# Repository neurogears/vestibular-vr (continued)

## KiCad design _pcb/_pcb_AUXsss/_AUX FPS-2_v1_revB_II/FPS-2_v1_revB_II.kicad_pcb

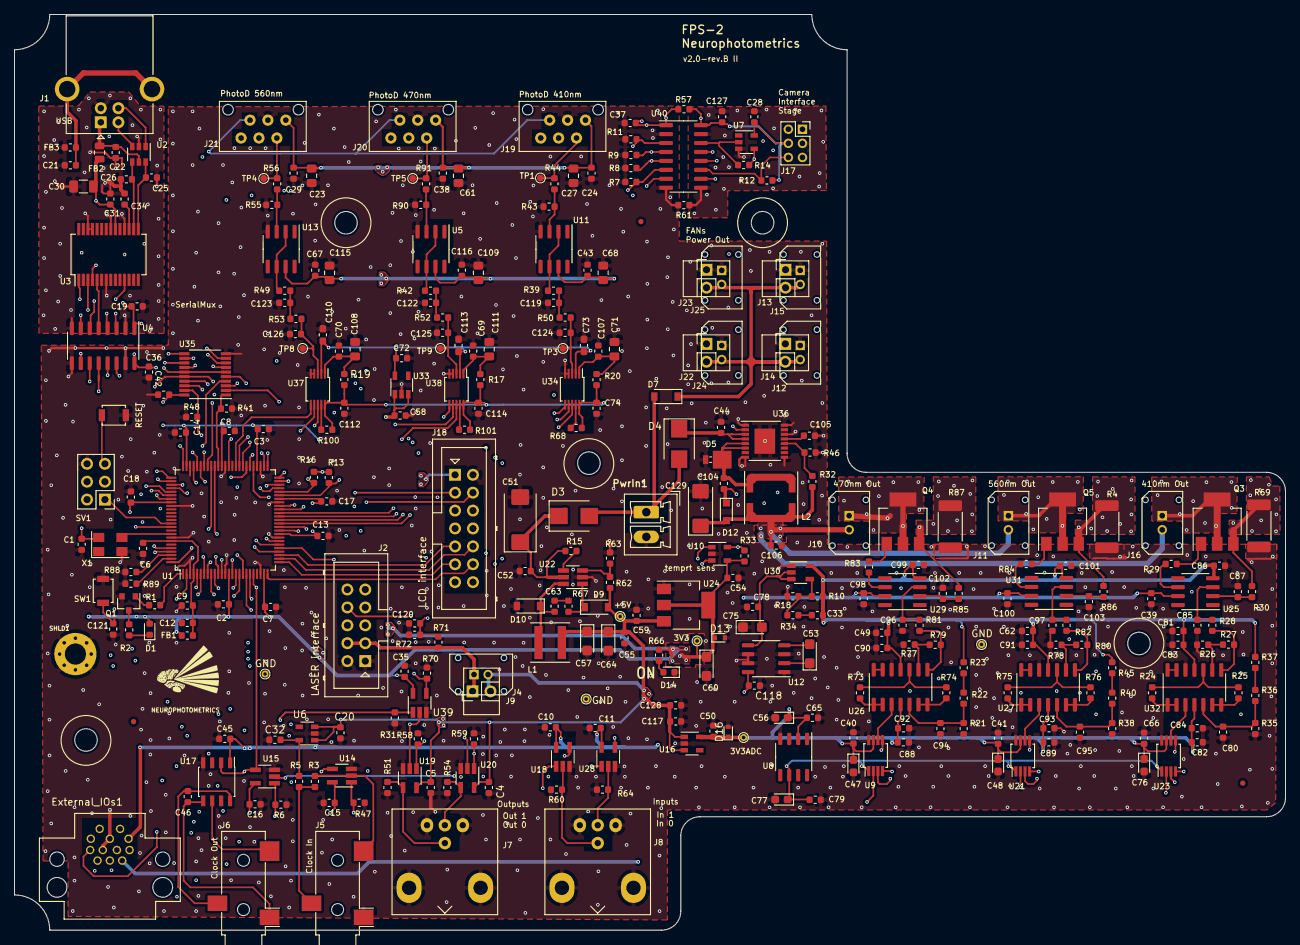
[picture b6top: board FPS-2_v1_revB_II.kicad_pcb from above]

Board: 4 copper layers, 180.4 x 130.0 mm, 335 parts (0 on the bottom side), 210 nets.

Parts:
Adafruit 2.8'' LCD: Adafruit_2.8''_LCD
C1, C2, C3, C4, C5, C6, C7, C8, C9, C10, C11, C13, C14, C15, C16, C17, C18, C19, C22, C24, C28, C29, C31, C34, C35, C36, C37, C38, C39, C40, C41, C42, C43, C45, C46, C52, C54, C55, C58, C63, C65, C66, C67, C69, C70, C72, C74, C79, C80, C83, C84, C86, C90, C91, C92, C93, C94, C95, C98, C99, C100, C101, C107, C112, C114, C116, C120, C121, C127, C128: 100n; C_0603_1608Metric
C12: 330n; C_0603_1608Metric
C20, C32, C49, C50, C62, C78, C81, C82, C88, C89, C106, C118: 4.7u 16V; C_0603_1608Metric
C21, C59: 4.7nF; C_0603_1608Metric
C23, C27, C61, C68, C71, C108, C109, C111, C115: 10u 16V; C_0805_2012Metric_Pad1.15x1.40mm_HandSolder
C25, C26: 47p; C_0603_1608Metric
C30: 4.7u 10V; C_1206_3216Metric
C33, C85, C87, C96, C97, C102, C103, C119, C122, C123, C124, C125, C126: DNI; C_0603_1608Metric
C44: 2.2u; C_0603_1608Metric
C47, C48, C56, C76, C77: 1u 25V; CP_EIA-2012-12_Kemet-R
C51: 10u 50V; CP_EIA-7343-20_Kemet-V_Pad2.25x2.55mm_HandSolder
C53, C57, C60, C64, C75: 10u 10V; CP_EIA-3216-18_Kemet-A
C73, C110, C113: 4.7u 16V; C_0603_1608Metric_Pad1.05x0.95mm_HandSolder
C104: 180nF; C_0603_1608Metric
C105: 2.2nF; C_0603_1608Metric
C117: 180pF; C_0603_1608Metric
C129: 100uF 25V; CP_EIA-6032-28_Kemet-C
D1, D14: GREEN LED; LED_0603_1608Metric
D3, D4: SSB43L-E3; D_SMB
D5: MBRM120; D_Powermite_AK
D7: SS14FL; D_SOD-123
D9: 1N4148W; D_SOD-123
D10: BAT42W-V; D_SOD-123
D12: CMDSH-3; D_SOD-323_HandSoldering
D13, D16: ESD9X3.3ST5G; D_SOD-523
External_IOs1: Conn_01x012; Phoenix_1424194_12pin
FB1: 330 R; R_0603_1608Metric
FB2: 40R@100MHz; R_0805_2012Metric
FB3: 600R/100MHz; R_0603_1608Metric
FID1, FID2, FID3: Fiducial; Fiducial_0.75mm_Mask1.5mm
G1: Neurophotometrics_Logo
J1: my_USB_B; my_USB_B_OST_USB-B1HSxx_Horizontal
J2: Conn_02x05_Odd_Even; Multicomp_MC9A12-1034_2x05_P2.54mm_Vertical
J4, J10, J11, J16: M80_1x2_2mmP; my_PinHeader_M80_1x2_2mmP
J5, J6: AudioJack2_Reference; my_Jack_3.5mm_CUI_SJ-3523-SMT_Horizontal
J7, J8: my_Conn_Coaxial_x2; my_2_BNC
J9, J13, J14, J22, J23: DNI; my_PinHeader_1x02_P2.54mm_Vertical
J12, J15, J24, J25: B2B plug; my_PinHeader_M80_1x2_2mmP
J17: Conn_02x03_Odd_Even; PinSocket_2x03_P2.00mm_Vertical
J18: Conn_02x07_Odd_Even; Multicomp_MC9A12-1434_2x07_P2.54mm_Vertical
J19, J20, J21: Molex_90325-3006
L1: 22uL; L_Coilcraft_XAL5030
L2: 2.6uL 1A; L_Coilcraft_XAL5030
Mech1, Mech2, Mech3, Mech4, Mech5: MountingHole_3.2mm_M3
PwrIn1: PowerIn; PhoenixContact_MCV_1,5_2-G-3.5_1x02_P3.50mm_Vertical
Q1: BC850; SOT-23
Q3, Q4, Q5: BCP56T1G; SOT-223-3_TabPin2
R1, R23, R37, R45: 1k; R_0603_1608Metric
R2, R66: 330R; R_0603_1608Metric
R3, R6, R7, R8, R9, R11, R31, R41, R47, R48, R51, R54, R58, R59, R60, R64, R70, R88, R89: 100k; R_0603_1608Metric
R4, R69, R87: 1R; R_2512_6332Metric_Pad1.52x3.35mm_HandSolder
R5, R17, R19, R20, R39, R42, R44, R49, R56, R91: 10R; R_0603_1608Metric
R10, R21, R35, R38: 5.76k; R_0603_1608Metric
R12, R33, R46, R63, R71: 10k; R_0603_1608Metric
R13: 2k8; R_0603_1608Metric
R14, R28, R29, R30, R50, R52, R53, R68, R81, R82, R83, R84, R85, R86, R100, R101: 0R; R_0603_1608Metric
R15: 1M; R_0603_1608Metric
R16, R34, R43, R55, R57, R61, R90: DNI; R_0603_1608Metric
R18: 86.6k; R_0603_1608Metric
R22, R36, R40, R72: 18k; R_0603_1608Metric
R24, R25, R26, R27, R73, R74, R75, R76, R77, R78, R79, R80: 4k7; R_0603_1608Metric
R32: 36k; R_0603_1608Metric
R62: 52.3k; R_0603_1608Metric
R67: 100R; R_0603_1608Metric
SHLD1: TestPoint_Probe; MountingHole_3mm_Pad_Via
SV1: MA03-2; PinHeader_2x03_P2.54mm_Vertical
SW1, SW2: SW_DIP_x01; SW_SPST_B3U-1000P
TP1, TP3, TP4, TP5, TP8, TP9: TestPoint; TestPoint_Pad_D1.0mm
TP10, TP20, TP21, TP22, TP23, TP24: TestPoint_Probe; TestPoint_THTPad_D1.0mm_Drill0.5mm
U1: ATxmega128A1U; TQFP-100_14x14mm_P0.5mm
U2: USBLC6-2; SOT-23-6
U3: FT232RL; SSOP-28_5.3x10.2mm_P0.65mm
U4: SI8642BC-B-IS1; SOIC-16_3.9x9.9mm_P1.27mm
U5, U11, U13: AD8655; SOIC-8_3.9x4.9mm_P1.27mm
U6: TLV70033_SOT23-5; SOT-23-5
U7: DNI; SOT-23-5
U8: MAX6162; SO-8_3.9x4.9mm_P1.27mm
U9, U21, U23: MAX5443; MSOP-8_3x3mm_P0.65mm
U10: Si7060; SOT-23-5
U12: MAX1680ESA+; SO-8_3.9x4.9mm_P1.27mm
U14, U15, U19, U20, U39: MC74VHC1GT126; SOT-23-5_HandSoldering
U16: TLV7433; SOT-23-5
U17: Si8610BC; SOIC-8_3.9x4.9mm_P1.27mm
U18, U28: SN74LVC1g125; SOT-23-5_HandSoldering
U22: MCP16301; SOT-23-6_Handsoldering
U24: LD1117S33TR; SOT-223-3_TabPin2
U25, U29, U31: AD8651; SOIC-8_3.9x4.9mm_P1.27mm
U26, U27, U32: OPA4170AIDR; SOIC-14_3.9x8.7mm_P1.27mm
U30: ADP7182AUJZ; TSOT-23-5
U33: TCR2LF; TSOT-23-5
U34, U37, U38: MCP33151D; MSOP-10_3x3mm_P0.5mm
U35: SN74ACT241; TSSOP-20_4.4x6.5mm_P0.65mm
U36: LT1765; TSSOP-16-1EP_4.4x5mm_P0.65mm
U40: SI8641; SOIC-16_3.9x9.9mm_P1.27mm
Wall: Stub_Wall
X1: DSC1001CI5-032; Crystal_SMD_5032-4Pin_5.0x3.2mm

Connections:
5V5_LEDS_POWER: C106.1, C129.1, D12.2, J10.2, J11.2, J16.2, L2.2, R32.1
+1V8: C72.1, C73.1, C110.1, C113.1, U33.5, U34.2, U37.2, U38.2
+3.3VDAC: C39.2, C40.2, C41.2, C47.1, C48.1, C50.2, C56.1, C65.2, C66.2, C76.1, C82.2, C84.2, C88.2, C89.2, C92.2, C93.2, C98.2, C100.2, C118.2, D16.1, TP10.1, U8.2, U9.7, U12.8, U16.5, U21.7, U23.7, U25.7, U26.4, U27.4, U29.7, U31.7, U32.4
+3.3VP: J5.R, R3.1, R5.1
+3V3: C1.2, C2.2, C3.2, C7.2, C8.2, C10.2, C11.2, C13.2, C14.2, C15.2, C16.2, C17.2, C18.2, C23.1, C24.1, C27.1, C29.1, C35.2, C36.2, C37.2, C38.1, C42.2, C43.1, C45.2, C54.2, C58.1, C60.1, C61.1, C67.1, C68.1, C74.1, C109.1, C112.1, C114.1, C115.1, C116.1, D1.2, D13.1, External_IOs1.9, FB1.2, J19.1, J20.1, J21.1, R13.2, R16.2, R17.1, R19.1, R20.1, R33.1, R57.2, R66.1, R68.1, R100.1, R101.1, SV1.2, TP24.1, U1.14, U1.24, U1.34, U1.44, U1.54, U1.64, U1.74, U1.83, U4.10, U4.16, U5.7, U10.4, U11.7, U13.7, U14.5, U15.5, U17.1, U18.5, U24.2, U28.5, U33.1, U33.3, U34.10, U35.20, U37.10, U38.10, U39.5, U40.1, U40.7, X1.4
+5V: C4.2, C5.2, C20.2, C55.1, C57.1, C59.1, C64.1, C117.2, C128.2, D9.2, J4.2, J9.2, J18.1, L1.2, R62.1, TP21.1, U6.1, U6.3, U16.1, U16.3, U19.5, U20.5, U24.3
-VDC: C33.2, C49.2, C62.2, C81.2, C83.2, C86.2, C90.2, C91.2, C99.2, C101.2, R10.1, R23.2, R37.2, R45.2, U25.4, U26.11, U27.11, U29.4, U30.5, U31.4, U32.11
/CLOCK_MASTER: J18.14, U1.21, U14.4, U15.4, U17.2
/COM_FROM_USB: J18.8, U1.66
/HOLD_COM: J18.7, U1.67
/I2C_SCL_port_Y: R16.1, U1.46, U10.3
/I2C_SDA_port_Y: R13.1, U1.45, U10.1
/IO_Interfaces/CAM_GND: C28.1, C127.1, J17.3, R61.1, U7.3, U40.9, U40.15
/IO_Interfaces/CAM_OUT_1: J17.1, U40.13
/IO_Interfaces/CAM_OUT_2: J17.2, U40.12
/IO_Interfaces/CAM_POWER: C28.2, C127.2, J17.4, R12.1, R57.1, U7.5, U40.10, U40.16
/IO_Interfaces/CAM_STROB_IN: J17.6, R12.2, U40.11
/IO_Interfaces/CAM_TRIG_OUT: R14.2, U7.2, U40.14
/IO_Interfaces/CAM_TRIG_OUT_BUFF: J17.5, R14.1, U7.4
/IO_Interfaces/CLOCK_IN: J5.T, R3.2, U14.2
/IO_Interfaces/CLOCK_OUT: J6.T, U17.6
/IO_Interfaces/CLOCK_OUT_GND: C46.1, J6.S, U17.5
/IO_Interfaces/CLOCK_OUT_Vcc: C46.2, J6.R, U17.8
/IO_Interfaces/FT_CTS: U3.11, U4.6
/IO_Interfaces/FT_RTS: U3.3, U4.4
/IO_Interfaces/FT_RXD: U3.5, U4.5
/IO_Interfaces/FT_TXD: U3.1, U4.3
/IO_Interfaces/LASER_Power: J2.3, J2.4, J4.1, J9.1, R71.1
/IO_Interfaces/LASER_TTL: J2.8, R70.2, U39.4
/IO_Interfaces/USB5V: C19.2, C30.1, C31.2, FB2.1, U3.4, U3.20, U4.1, U4.7
/IO_Interfaces/USBDM: C26.2, U2.4, U3.16
/IO_Interfaces/USBDP: C25.2, U2.6, U3.15
/LCD_CLCK_OUT: J18.13, U15.2
/LCD_Clock_Out_ENBL: R6.1, U1.6, U15.1
/LEDs_output_Interface/-3V3: C75.2, C78.2, U12.5, U30.2, U30.3
/LEDs_output_Interface/CURR_410nm: U23.6, U32.3
/LEDs_output_Interface/CURR_470nm: U9.6, U26.3
/LEDs_output_Interface/CURR_560nm: U21.6, U27.3
/LEDs_output_Interface/LED_CTRL_410nm: R27.2, R28.1, U32.8
/LEDs_output_Interface/LED_CTRL_470nm: R79.2, R81.1, U26.8
/LEDs_output_Interface/LED_CTRL_560nm: R80.2, R82.1, U27.8
/LEDs_output_Interface/Vref_2.048V: C77.1, C79.2, U8.6, U9.1, U21.1, U23.1
/MASTER_CTS: J18.12, U1.25
/MASTER_RTS: J18.11, U1.26
/MASTER_RXD: J18.10, U1.27
/MASTER_TXD: J18.9, U1.28
/PDI_CLK: SV1.5, SW2.2, U1.90
/PDI_DATA: SV1.1, U1.89
/PSU_Stage/FAN_POWER: D7.1, J12.2, J13.2, J14.2, J15.2, J22.2, J23.2, J24.2, J25.2
/PhotoD_410nm_SPI_MISO: U1.38, U34.7
/PhotoD_410nm_SPI_SCLK: U1.37, U34.8
/PhotoD_470nm_SPI_MISO: U1.40, U38.7
/PhotoD_470nm_SPI_SCLK: U1.39, U38.8
/PhotoD_560nm_SPI_MISO: U1.42, U37.7
/PhotoD_560nm_SPI_SCLK: U1.41, U37.8
/PhotoDiodes input Interface/PhotodiodeLP_410nm: C124.1, R50.2, TP3.1, U34.3
/PhotoDiodes input Interface/PhotodiodeLP_470nm: C125.1, R52.2, TP9.1, U38.3
/PhotoDiodes input Interface/PhotodiodeLP_560nm: C126.1, R53.2, TP8.1, U37.3
/PhotoDiodes input Interface/PhotodiodeOutput_410nm: J19.2, R44.2, TP1.1
/PhotoDiodes input Interface/PhotodiodeOutput_470nm: J20.2, R91.1, TP5.1
/PhotoDiodes input Interface/PhotodiodeOutput_560nm: J21.2, R56.2, TP4.1
/aux_IO1: R88.2, U1.98
/aux_IO2: R89.2, U1.99
/mux_CTS: U4.13, U35.8, U35.17
/mux_RTS: U4.11, U35.7, U35.16
/mux_RXD: U4.14, U35.6, U35.15
/mux_TXD: U4.12, U35.9, U35.18
/tempert_ALARM1: R33.2, U1.69, U10.5
/u_CAM_OUT_1: R9.2, U1.50, U40.4
/u_CAM_OUT_2: R8.2, U1.49, U40.5
/u_CAM_STROB_IN: R7.2, U1.57, U40.6
/u_CAM_TRIG_OUT: R11.2, U1.15, U40.3
/u_CTS_0: U1.71, U35.12
/u_CTS_1: J18.5, U35.3
/u_Clck_In_Enable: R47.1, U1.5, U14.1
/u_DigPot_410_~CS: J19.4, U1.68
/u_DigPot_470_~CS: J20.4, U1.70
/u_DigPot_560_~CS: J21.4, U1.72
/u_DigPot_SPI_CLCK: J19.6, J20.6, J21.6, U1.76
/u_DigPot_SPI_SDO: J19.5, J20.5, J21.5, U1.77
/u_External_IO_1: External_IOs1.1, U1.29
/u_External_IO_2: External_IOs1.3, U1.31
/u_External_IO_3: External_IOs1.5, U1.51
/u_External_IO_4: External_IOs1.12, U1.52
/u_External_IO_5: External_IOs1.2, U1.96
/u_External_IO_6: External_IOs1.4, U1.97
/u_External_UART_Rx: External_IOs1.6, U1.17
/u_External_UART_Tx: External_IOs1.8, U1.18
/u_In6: U1.56, U18.4
/u_In6_Enbl: U1.80, U18.1
/u_In7: U1.81, U28.4
/u_In7_Enbl: U1.82, U28.1
/u_LASER_state_ON_OFF: C120.2, R71.2, R72.1, U1.100
/u_LEDs_DAC_SPI_CLK_out: U1.32, U9.3, U21.3, U23.3
/u_LEDs_DAC_SPI_MOSI: U1.30, U9.4, U21.4, U23.4
/u_Out4: U1.35, U19.2, U39.2
/u_Out4_Enbl: R58.2, U1.78, U19.1
/u_Out5: U1.36, U20.2
/u_Out5_Enbl: R59.2, U1.79, U20.1
/u_Out6_LASER_ENBL: R31.2, U1.55, U39.1
/u_PhotoD_ADC_ConverStart_410nm: U1.58, U34.6
/u_PhotoD_ADC_ConverStart_470nm: U1.59, U38.6
/u_PhotoD_ADC_ConverStart_560nm: U1.60, U37.6
/u_RTS_0: U1.75, U35.4
/u_RTS_1: J18.6, U35.13
/u_RXD_0: U1.47, U35.14
/u_RXD_1: J18.3, U35.5
/u_STATE_LED: R1.1, U1.1
/u_TXD_0: U1.48, U35.2
/u_TXD_1: J18.4, U35.11
/u_interface_select_1: R41.2, U1.65, U35.1
/u_interface_select_2: R48.2, U1.62, U35.19
/u_test_switch_1: C121.2, SW1.1, U1.2
/~u_DAC_CLR_410nm: U1.8, U23.5
/~u_DAC_CLR_470nm: U1.12, U9.5
/~u_DAC_CLR_560nm: U1.10, U21.5
/~u_DAC_CS_410nm: U1.7, U23.2
/~u_DAC_CS_470nm: U1.11, U9.2
/~u_DAC_CS_560nm: U1.9, U21.2
/~u_LASER_CS: J2.5, U1.16
/~u_LASER_SPI_CLCK: J2.6, U1.19
/~u_LASER_SPI_DATA: J2.7, U1.20
GNDD: C1.1, C2.1, C3.1, C4.1, C5.1, C6.1, C7.1, C8.1, C9.1, C10.1, C11.1, C12.1, C13.1, C14.1, C15.1, C16.1, C17.1, C18.1, C20.1, C23.2, C24.2, C27.2, C29.2, C32.1, C35.1, C36.1, C37.1, C38.2, C39.1, C40.1, C41.1, C42.1, C43.2, C44.2, C45.1, C47.2, C48.2, C49.1, C50.1, C51.2, C52.2, C54.1, C55.2, C56.2, C57.2, C58.2, C59.2, C60.2, C61.2, C62.1, C64.2, C65.1, C66.1, C67.2, C68.2, C69.2, C70.2, C71.2, C72.2, C73.2, C74.2, C75.1, C76.2, C77.2, C78.1, C79.1, C80.1, C81.1, C82.1, C83.1, C84.1, C85.1, C86.1, C87.1, C88.1, C89.1, C90.1, C91.1, C92.1, C93.1, C94.1, C95.1, C96.1, C97.1, C98.1, C99.1, C100.1, C101.1, C102.1, C103.1, C105.2, C106.2, C107.2, C108.2, C109.2, C110.2, C111.2, C112.2, C113.2, C114.2, C115.2, C116.2, C117.1, C118.1, C119.2, C120.1, C121.1, C122.2, C123.2, C124.2, C125.2, C126.2, C128.1, C129.2, D5.2, D10.2, D13.2, D14.1, D16.2, External_IOs1.10, External_IOs1.11, J2.1, J2.2, J5.S, J7.3, J8.3, J12.1, J13.1, J14.1, J15.1, J18.2, J19.3, J20.3, J21.3, J22.1, J23.1, J24.1, J25.1, PwrIn1.2, Q1.2, R4.2, R6.2, R7.1, R8.1, R9.1, R11.1, R18.1, R21.1, R26.1, R31.1, R35.1, R38.1, R41.1, R43.1, R46.2, R47.2, R48.1, R51.1, R54.1, R55.1, R58.1, R59.1, R60.2, R61.2, R63.2, R64.2, R69.2, R70.1, R72.2, R77.1, R78.1, R87.2, R88.1, R89.1, R90.1, SHLD1.1, SV1.6, SW1.2, SW2.1, TP20.1, TP22.1, TP23.1, U1.3, U1.13, U1.23, U1.33, U1.43, U1.53, U1.63, U1.73, U1.84, U1.93, U4.9, U4.15, U5.4, U6.2, U8.4, U9.8, U10.2, U11.4, U12.1, U12.3, U12.6, U12.7, U13.4, U14.3, U15.3, U16.2, U17.4, U18.3, U19.3, U20.3, U21.8, U22.2, U23.8, U24.1, U26.12, U27.12, U28.3, U30.1, U32.12, U33.2, U34.4, U34.5, U35.10, U36.1, U36.8, U36.9, U36.14, U36.16, U36.17, U37.4, U37.5, U38.4, U38.5, U39.3, U40.2, U40.8, X1.2
GNDREF: C19.1, C21.1, C22.1, C25.1, C26.1, C30.2, C31.1, C34.1, FB3.1, J1.4, U2.2, U3.7, U3.18, U3.21, U3.25, U3.26, U4.2, U4.8
unnamed: C6.2, C9.2, C12.2, FB1.1, U1.4, U1.94
unnamed: C21.2, FB3.2, J1.5
unnamed: C22.2, FB2.2, J1.1, U2.5
unnamed: C32.2, R5.2, U6.5
unnamed: C33.1, R34.1
unnamed: C34.2, U3.17
unnamed: C44.1, D4.1, U36.3, U36.4
unnamed: C51.1, C52.1, D3.1, R15.1, U22.5
unnamed: C53.1, U12.2
unnamed: C53.2, U12.4
unnamed: C63.1, D10.1, L1.1, U22.6
unnamed: C63.2, R67.2
unnamed: C80.2, R35.2, R36.1, U32.5
unnamed: C85.2, R28.2, U25.3
unnamed: C87.2, R30.1, U25.2
unnamed: C94.2, R21.2, R22.1, U26.5
unnamed: C95.2, R38.2, R40.1, U27.5
unnamed: C96.2, R81.2, U29.3
unnamed: C97.2, R82.2, U31.3
unnamed: C102.2, R85.1, U29.2
unnamed: C103.2, R86.1, U31.2
unnamed: C104.1, D12.1, U36.2
unnamed: C104.2, D5.1, L2.1, U36.5, U36.6
unnamed: C105.1, U36.13
unnamed: C71.1, C107.1, R20.2, U34.1
unnamed: C70.1, C108.1, R19.2, U37.1
unnamed: C69.1, C111.1, R17.2, U38.1
unnamed: C119.1, R39.2, R50.1
unnamed: C122.1, R42.2, R52.1
unnamed: C123.1, R49.2, R53.1
unnamed: D1.1, R2.1
unnamed: D9.1, R67.1, U22.1
unnamed: D14.2, R66.2
unnamed: J1.2, U2.3
unnamed: J1.3, U2.1
unnamed: J7.1, R51.2, U19.4
unnamed: J7.2, R54.2, U20.4
unnamed: J8.1, R60.1, U18.2
unnamed: J8.2, R64.1, U28.2
unnamed: J10.1, Q4.2
unnamed: J11.1, Q5.2
unnamed: J16.1, Q3.2
unnamed: Q1.1, R1.2
unnamed: Q1.3, R2.2
unnamed: Q3.1, R29.2
unnamed: Q3.3, R30.2, R69.1
unnamed: Q4.1, R83.2
unnamed: Q4.3, R85.2, R87.1
unnamed: Q5.1, R84.2
unnamed: Q5.3, R4.1, R86.2
unnamed: R10.2, R18.2, R34.2, U30.4
unnamed: R15.2, U22.4
unnamed: R22.2, R23.1
unnamed: R24.1, U32.1, U32.2
unnamed: R24.2, R25.2, U32.10
unnamed: R25.1, U32.6, U32.7
unnamed: R26.2, R27.1, U32.9
unnamed: R29.1, U25.6
unnamed: R32.2, R46.1, U36.12
unnamed: R36.2, R37.1
unnamed: R39.1, U11.2, U11.6
unnamed: R40.2, R45.1
unnamed: R42.1, U5.2, U5.6
unnamed: R43.2, R44.1, U11.3
unnamed: R49.1, U13.2, U13.6
unnamed: R55.2, R56.1, U13.3
unnamed: R62.2, R63.1, U22.3
unnamed: R68.2, U34.9
unnamed: R73.1, U26.1, U26.2
unnamed: R73.2, R74.2, U26.10
unnamed: R74.1, U26.6, U26.7
unnamed: R75.1, U27.1, U27.2
unnamed: R75.2, R76.2, U27.10
unnamed: R76.1, U27.6, U27.7
unnamed: R77.2, R79.1, U26.9
unnamed: R78.2, R80.1, U27.9
unnamed: R83.1, U29.6
unnamed: R84.1, U31.6
unnamed: R90.2, R91.2, U5.3
unnamed: R100.2, U37.9
unnamed: R101.2, U38.9
unnamed: U1.92, X1.3
unnamed: U26.13, U26.14
unnamed: U27.13, U27.14
unnamed: U32.13, U32.14
POWER_IN: D3.2, D4.2, D7.2, External_IOs1.7, PwrIn1.1

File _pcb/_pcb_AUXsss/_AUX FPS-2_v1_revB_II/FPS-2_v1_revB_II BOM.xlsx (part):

Source: | Z:\My Drive\projects\fiber photometry system v2 (FPS-2)\pcb\FPS-2_v1_revB_I\FPS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
Date: | 43894.601006944446
Tool: | Eeschema (5.1.4)-1
Generator: | C:\Program Files\KiCad\bin\scripting\plugins/_my_bom_csv_grouped_Value_FootPrin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
Component Count: | 325
Ref | Qnty | Value | Footprint | Comment | Comment2 | Mnfct | MnfctCode | Provider | ProviderCode
C1, C6, C18, C14, C17, C8, C3, C13, C7, C2, C9, C42, C121, C52, C63, C55, C36, 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 | 70 | 100n | Capacitor_SMD:C_0603_1608Metric | 100n 50V | - | Yageo | CC603KRX7R9BB104 | Mouser | 603-CC603KRX7R9BB104
C12, | 1 | 330n | Capacitor_SMD:C_0603_1608Metric | 330n 50V | - | TDK | CGA3E3X5R1H334K080AB | Mouser | 810-CGA3E3X5R1H334KB
C26, C25, | 2 | 47p | Capacitor_SMD:C_0603_1608Metric | 47pF 50V C0G 5% | - | AVX | 06035A470JAT2A | Mouser | 581-06035A470J
C30, | 1 | 4.7u 10V | Capacitor_SMD:C_1206_3216Metric | CAP TANT 4.7uF 10V 10% | - | AVX | TAJA475K010 | Mouser | 581-TAJA475K010
C44, | 1 | 2.2u | Capacitor_SMD:C_0603_1608Metric | 2.2uF | - | Yageo | GRM188R61E225MA12D | Mouser | 81-GRM188R61E225MA2D
C51, | 1 | 10u 50V | Capacitor_Tantalum_SMD:CP_EIA-7343-20_Kemet-V_Pad2.25x2.55mm_HandSolder | 10u 50V 20% | - | AVX | T521D106M050ATE090 | Mouser | 80-T521D106M50ATE90
C56, C77, C76, C48, C47, | 5 | 1u 25V | Capacitor_Tantalum_SMD:CP_EIA-2012-12_Kemet-R | - | - | AVX | TPSR105K025R2500 | Mouser | 581-TPSR105K025R2500
C59, C21, | 2 | 4.7nF | Capacitor_SMD:C_0603_1608Metric | 4.7nF 50V X7R 10% | - | AVX | 06035C472KAT2A | Mouser | 581-06035C472K
C60, C57, C64, C53, C75, | 5 | 10u 10V | Capacitor_Tantalum_SMD:CP_EIA-3216-18_Kemet-A | Tantalum Capacitors - 10uF 10volts 20% A Case | - | Vishay | T55A106M010C0300 | Mouser | 74-T55A106M010C0300
C68, C115, C23, C108, C27, C111, C61, C71, C109, | 9 | 10u 16V | Capacitor_SMD:C_0805_2012Metric_Pad1.15x1.40mm_HandSolder | - | - | Taiyo Yuden | EMK212ABJ106MG-T | Mouser | 963-EMK212ABJ106MG-T
C73, C113, C110, | 3 | 4.7u 16V | Capacitor_SMD:C_0603_1608Metric_Pad1.05x0.95mm_HandSolder | Multilayer Ceramic SMD 0603 16V 4.7uF X6S | - | TDK | C1608X6S1C475K080AC | Mouser | 810-C1608X6S1C475K
C97, C103, C96, C102, C87, C85, C33, C123, C126, C122, C125, C119, C124, | 13 | DNI | Capacitor_SMD:C_0603_1608Metric | - | - | - | - | - | -
C104, | 1 | 180nF | Capacitor_SMD:C_0603_1608Metric | - | - | Murata Electronics | GRM188R71E184KA88D | Mouser | 81-GRM188R71E184KA8D
C105, | 1 | 2.2nF | Capacitor_SMD:C_0603_1608Metric | 2.2n | - | KEMET | C0603C222K3RACTU | Mouser | 80-C0603C222K3R
C106, C20, C32, C78, C89, C62, C88, C49, C81, C82, C50, C118, | 12 | 4.7u 16V | Capacitor_SMD:C_0603_1608Metric | Multilayer Ceramic SMD 0603 16V 4.7uF X6S | - | TDK | C1608X6S1C475K080AC | Mouser | 810-C1608X6S1C475K
C117, | 1 | 180pF | Capacitor_SMD:C_0603_1608Metric | 180pF 50V 5% | - | Yageo | C0603C181J5GACTU | Mouser | 80-C0603C181J5G
D1, D14, | 2 | GREEN LED | LED_SMD:LED_0603_1608Metric | Power On LED | - | Vishay | TLMP1100-GS08 | Mouser | 78-TLMP1100-GS08
D3, D4, | 2 | SSB43L-E3 | Diode_SMD:D_SMB | - | - | Vishay | SSB43L-E3/52T | Mouser | 625-SSB43L-E3
D5, | 1 | MBRM120 | Diode_SMD:D_Powermite_AK | ESD Protection Diode; | ref value UPS20 old; update to MBRM120LT3G | On Semiconductor | MBRM120LT3G | Mouser | 863-MBRM120LT3G
D7, | 1 | SS14FL | Diode_SMD:D_SOD-123 | - | - | ON Semiconductor | SS14FL | Mouser | 512-SS14FL
D9, | 1 | 1N4148W | Diode_SMD:D_SOD-123 | Diodes - General Purpose, Power, Switching 100 Volt 500mA 4ns | - | Vishay | 1N4148W-E3-18 | Mouser | 78-1N4148W-E3-18
D10, | 1 | BAT42W-V | Diode_SMD:D_SOD-123 | ESD Protection Diode | - | Vishay | BAT42W-G3-08 | Mouser | 78-BAT42W-G3-08
D12, | 1 | CMDSH-3 | Diode_SMD:D_SOD-323_HandSoldering | CMDSH-3 | - | Central Semiconductor | CMDSH-3 TR | Mouser | 610-CMDSH-3
D13, D16, | 2 | ESD9X3.3ST5G | Diode_SMD:D_SOD-523 | Low Voltage Transil =3V3 | - | ON Semiconductor | ESD9X3.3ST5G | Mouser | 863-ESD9X3.3ST5G
External_IOs1, | 1 | Conn_01x012 | FPS_pads_lib:Phoenix_1424194_12pin | TO BE SURE ABOUT THIS PLUG - MECHANICALLY & ELECTRICALLY | - | Phoenix Contact | 1424194 | Mouser | 651-1424194
F1, | 1 | 600R/100MHz | Resistor_SMD:R_0603_1608Metric | - | - | Yageo | BLM18KG601SN1D | Mouser | 81-BLM18KG601SN1D
FB1, | 1 | 330 R | Resistor_SMD:R_0603_1608Metric | Ferrite Beads 330ohms Power Supply | - | Murata Electronics | BLM18SG331TN1D | Mouser | 81-BLM18SG331TN1D
FB2, | 1 | 40R@100MHz | Resistor_SMD:R_0805_2012Metric | USB ferrite bead | - | Laird Performance Materials | MI0805K400R-10 | Mouser | 875-MI0805K400R-10
FID1, FID2, FID3, | 3 | Fiducial | Fiducial:Fiducial_0.75mm_Mask1.5mm | - | - | n.a. | n.a. | n.a. | n.a.
J1, | 1 | my_USB_B | FPS_pads_lib:my_USB_B_OST_USB-B1HSxx_Horizontal | USB B | - | Amphenol FCI | 61729-1011BLF | Mouser | 649-61729-1011BLF
J2, | 1 | Conn_02x05_Odd_Even | Connector_Multicomp:Multicomp_MC9A12-1034_2x05_P2.54mm_Vertical | LASER Header Interface 10P 4WALL GLDFL | - | 3M Electronic Solutions Division | 30310-6002HB | Mouser | 517-30310-6002
J4, J16, J11, J10, | 4 | M80_1x2_2mmP | FPS_pads_lib:my_PinHeader_M80_1x2_2mmP | 560nm output | - | Phoenix Contact | M80-8820242 | Mouser | 855-M80-8820242
J5, J6, | 2 | AudioJack2_Reference | FPS_pads_lib:my_Jack_3.5mm_CUI_SJ-3523-SMT_Horizontal | Clock_Out Jack | - | Switchcraft | 35RASMT2BHNTRX | Mouser | 502-35RASMT2BHNTRX
J8, J7, | 2 | my_Conn_Coaxial_x2 | FPS_pads_lib:my_2_BNC | BNC panel connectors | - | Amphenol RF | 031-6575 | Mouser | 523-31-6575
J12, J15, J24, J25, | 4 | B2B plug | FPS_pads_lib:my_PinHeader_M80_1x2_2mmP | FAN output plug | - | JST Sales America | B2B-XH-A-GU | Digikey | 455-2946-ND
J13, J14, J22, J23, J9, | 5 | DNI | FPS_pads_lib:my_PinHeader_1x02_P2.54mm_Vertical | 1x02_P2.54mm_Vertical; different pitch | Fan extra Power plug | - | - | - | -
J17, | 1 | Conn_02x03_Odd_Even | Connector_PinSocket_2.00mm:PinSocket_2x03_P2.00mm_Vertical | Headers Housings 3+3 POS VERT | - | Harwin | M80-8530642 | Mouser | 855-M80-8530642
J18, | 1 | Conn_02x07_Odd_Even | Connector_Multicomp:Multicomp_MC9A12-1434_2x07_P2.54mm_Vertical | LCD Header Interface | - | 3M Electronic Solutions Division | N2514-6002RB | Mouser | 517-N2514-6002RB
J19, J21, J20, | 3 | Molex_90325-3006 | FPS_pads_lib:Molex_90325-3006 | PhotoDiode plug | Headers & Wire Housings 1.27MM 6P RA HDR LO-PRO W/PCB PEGS | Molex | 90325-3006 | Mouser | 538-90325-3006
L1, | 1 | 22uL | Inductor_SMD:L_Coilcraft_XAL5030 | Fixed Inductors 22uH 20% 830mA | - | Vishay | IFSC1515AHER220M01 | Mouser | 70-IFSC1515AHER220M0
L2, | 1 | 2.6uL 1A | FPS_pads_lib:L_Coilcraft_XAL5030 | Low Profile, High Current Inductors | - | Bourns | SRR5028-2R6Y | Mouser | 652-SRR5028-2R6Y
PwrIn1, | 1 | PowerIn | Connector_Phoenix_MC:PhoenixContact_MCV_1,5_2-G-3.5_1x02_P3.50mm_Vertical | Main Power In | - | Phoenix Contact | 1843606 | Mouser | 651-1843606
Q1, | 1 | BC850 | Package_TO_SOT_SMD:SOT-23 | Transt auxiliar LED driver | - | Nexperia | BC850C,215 | Mouser | 771-BC850C-T/R
Q3, Q5, Q4, | 3 | BCP56T1G | Package_TO_SOT_SMD:SOT-223-3_TabPin2 | BJT 1A 100V NPN | - | ON Semiconductor | BCP56T1G | Mouser | 863-BCP56T1G
R1, R45, R37, R23, | 4 | 1k | Resistor_SMD:R_0603_1608Metric | - | - | Yageo | RC0603FR-071KL | Mouser | 603-RC0603FR-071KL
R2, R66, | 2 | 330R | Resistor_SMD:R_0603_1608Metric | - | - | Vishay | CRCW0603330RFKEAC | Mouser | 71-CRCW0603330RFKEAC
R5, R56, R91, R44, R20, R17, R19, R49, R42, R39, | 10 | 10R | Resistor_SMD:R_0603_1608Metric | - | - | Panasonic | ERJ-3EKF10R0V | Mouser | 667-ERJ-3EKF10R0V
R10, R38, R35, R21, | 4 | 5.76k | Resistor_SMD:R_0603_1608Metric | - | - | Yageo | RC0603FR-075K76L | Mouser | 603-RC0603FR-075K76L
R13, | 1 | 2k8 | Resistor_SMD:R_0603_1608Metric | - | - | Panasonic | ERJ-3EKF2801V | Mouser | 667-ERJ-3EKF2801V
R14, R82, R84, R86, R81, R83, R85, R30, R29, R28, R100, R101, R68, R53, R52, R5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 | 16 | 0R | Resistor_SMD:R_0603_1608Metric | - | - | Yageo | RC0603FR-070RL | Mouser | 603-RC0603FR-070RL
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
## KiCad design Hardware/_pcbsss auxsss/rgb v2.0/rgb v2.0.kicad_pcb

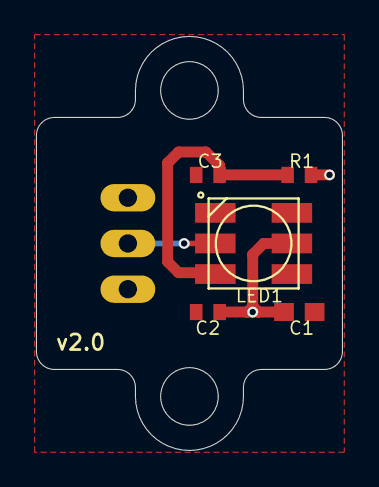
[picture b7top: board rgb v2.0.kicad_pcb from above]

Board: 2 copper layers, 17.0 x 23.0 mm, 8 parts (1 on the bottom side), 4 nets.

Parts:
@HOLE0, @HOLE1: (no value)
C1: 10uF; C0603
C2, C3: 100nF; C0402
J1: 22-05-7038-03; 7395-03
LED1: WS2812LARGER; WS2812_LARGER
R1: 33; R0402

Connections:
+5V: C1.1, C2.1, J1.1, LED1.LEDVDD, R1.2
GND: C1.2, C2.2, C3.2, J1.3, LED1.VSS
unnamed: C3.1, LED1.VDD, R1.1
SERIAL_LED0: J1.2, LED1.DI

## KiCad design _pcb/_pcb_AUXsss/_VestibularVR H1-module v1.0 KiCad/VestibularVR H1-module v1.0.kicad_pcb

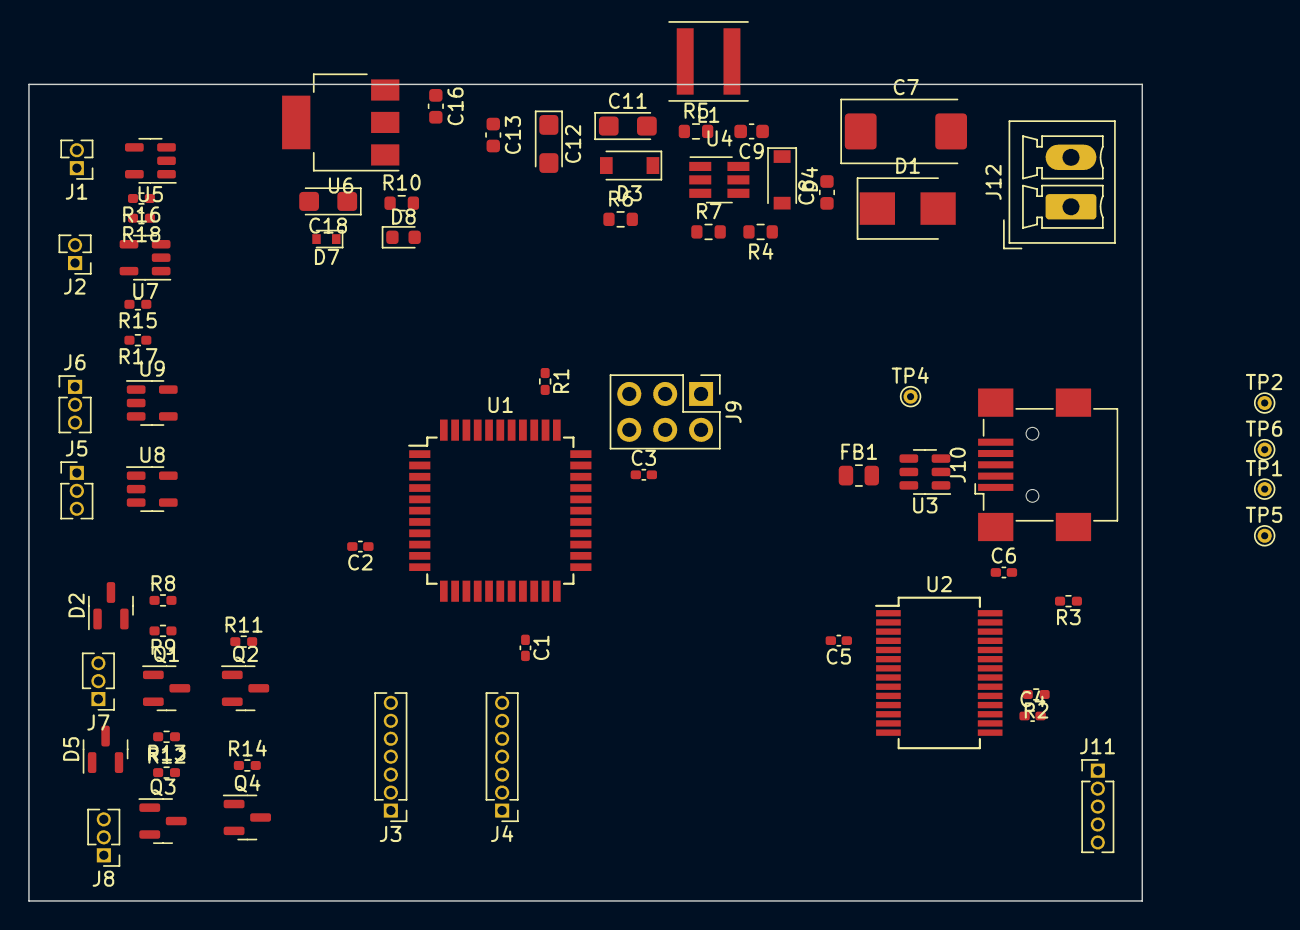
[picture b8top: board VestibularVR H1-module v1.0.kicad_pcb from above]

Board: 2 copper layers, 78.8 x 57.8 mm, 71 parts (0 on the bottom side), 43 nets, no tracks yet.

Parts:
C1, C2, C3, C4, C5: 100n; C_0402_1005Metric_Pad0.74x0.62mm_HandSolder
C6: 4.7nF; C_0402_1005Metric_Pad0.74x0.62mm_HandSolder
C7: 10u 50V; CP_EIA-7343-20_Kemet-V_Pad2.25x2.55mm_HandSolder
C8, C9, C13: 100n; C_0603_1608Metric
C11, C12, C18: 10u 10V; CP_EIA-3216-18_Kemet-A
C16: 4.7nF; C_0603_1608Metric
D1: SSB43L-E3; D_SMB
D2, D5: BZX84C51-7-F; SOT-23
D3: 1N4148W; D_SOD-123
D4: BAT42W-V; D_SOD-123
D7: ESD9X3.3ST5G; D_SOD-523
D8: GREEN LED; LED_0603_1608Metric
FB1: 40R@100MHz; R_0805_2012Metric
J1: Camera1_trigger; PinHeader_1x02_P1.27mm_Vertical
J2: Camera2_trigger; PinHeader_1x02_P1.27mm_Vertical
J3: Optical flow 1; PinHeader_1x07_P1.27mm_Vertical
J4: Optical flow 2; PinHeader_1x07_P1.27mm_Vertical
J5: Lick_port_1; PinHeader_1x03_P1.27mm_Vertical
J6: Lick_port_2; PinHeader_1x03_P1.27mm_Vertical
J7: reward valve 1; PinHeader_1x03_P1.27mm_Vertical
J8: reward valve 2; PinHeader_1x03_P1.27mm_Vertical
J9: Conn_02x03_Odd_Even; PinHeader_2x03_P2.54mm_Vertical
J10: USB_B; USB_Mini-B_Wuerth_65100516121_Horizontal
J11: H1 board IOs; PinHeader_1x05_P1.27mm_Vertical
J12: PowerIn; PhoenixContact_MCV_1,5_2-G-3.5_1x02_P3.50mm_Vertical
L1: 22uL; L_Coilcraft_XAL5030
Q1, Q3: NDS332P; SOT-23
Q2, Q4: DMN2005K; SOT-23
R1: DNI 10k; R_0402_1005Metric_Pad0.72x0.64mm_HandSolder
R2: 10k; R_0402_1005Metric_Pad0.72x0.64mm_HandSolder
R3: 1M; R_0402_1005Metric_Pad0.72x0.64mm_HandSolder
R4: 1M; R_0603_1608Metric
R5: 100R; R_0603_1608Metric
R6: 52.3k; R_0603_1608Metric
R7: 10k; R_0603_1608Metric
R8, R12: 470; R_0402_1005Metric_Pad0.72x0.64mm_HandSolder
R9, R13: 1k; R_0402_1005Metric_Pad0.72x0.64mm_HandSolder
R10: 330R; R_0603_1608Metric
R11, R14: 4k7; R_0402_1005Metric_Pad0.72x0.64mm_HandSolder
R15, R16, R17, R18: DNI 0R; R_0402_1005Metric_Pad0.72x0.64mm_HandSolder
TP1, TP2, TP4, TP5, TP6: TestPoint_Probe; TestPoint_THTPad_D1.0mm_Drill0.5mm
U1: ATxmega32A4U-A; TQFP-44_10x10mm_P0.8mm
U2: FT232RL; SSOP-28_5.3x10.2mm_P0.65mm
U3: USBLC6-2SC6; SOT-23-6
U4: MCP16301; SOT-23-6_Handsoldering
U5, U7, U8, U9: 74LVC1G07; SOT-23-5
U6: LD1117S33TR; SOT-223-3_TabPin2

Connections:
+3.3V: C1.1, C2.1, C3.1, C5.1, J3.1, J4.1, J5.1, J6.1, J9.2, R1.1, R2.1, R17.1, R18.1, U1.9 (VCC), U1.19 (VCC), U1.31 (VCC), U2.4 (VCCIO)
+3V3: C18.1, D7.1 (K), R10.1, TP2.1, U6.2 (VO)
+5V: C11.1, C12.1, C13.1, C16.1, D3.2 (A), L1.2, R6.1, R15.1, R16.1, TP1.1, U6.3 (VI)
+5VP: FB1.1, U2.20 (VCC)
+12V: D1.2 (A), J11.1, J12.1, Q1.2 (D), Q3.2 (D), R9.1, R13.1
/Cam1_trigger_out: J1.2, U5.4
/Cam2_trigger_out: J2.2, U7.4
/FTDI_CTS: U1.28 (PE0/SDA), U2.11 (~CTS)
/FTDI_RTS: U1.29 (PE1/XCK0/SCL), U2.3 (~RTS)
/FTDI_RXD: U1.33 (PE3/TXD0), U2.5 (RXD)
/FTDI_TXD: U1.32 (PE2/RXD0), U2.1 (TXD)
/Lick_port_1_in: J5.2, U8.2
/Lick_port_2_in: J6.2, U9.2
/PDI_CLK: J9.5, R1.2, U1.35 (~RESET/PDI_CLK)
/PDI_DATA: J9.1, U1.34 (PDI_DATA)
/USB D+: U2.15 (USBDP), U3.4 (I/O2)
/USB D-: U2.16 (USBDM), U3.6 (I/O1)
/plug USB D+: J10.3, U3.3 (I/O2)
/plug USB D-: J10.2, U3.1 (I/O1)
/plug USB power: FB1.2, J10.1, U3.5 (VBUS)
/reward_valve_1: D2.1 (K), Q1.3 (S)
/reward_valve_2: D5.1 (K), Q3.3 (S)
/u_Cam1_trigger: U1.4 (PB0/ADC8/AREFB), U5.2
/u_Cam2_trigger: U1.5 (PB1/ADC9), U7.2
/u_Lick_port_2: U1.41 (PA1/ADC1), U9.4
/u_reward_valve_1: Q2.1 (G), R11.1, U1.2 (PA6/ADC6)
/u_reward_valve_2: Q4.1 (G), R14.1, U1.3 (PA7/ADC7)
GND: C1.2, C2.2, C3.2, C4.2, C5.2, C6.2, C7.2, C8.2, C11.2, C12.2, C13.2, C16.2, C18.2, D2.3 (A), D4.2 (A), D5.3 (A), D7.2 (A), D8.1 (K), J1.1, J2.1, J3.7, J4.7, J5.3, J6.3, J7.1, J8.1, J9.6, J10.5, J11.2, J12.2, Q2.2 (S), Q4.2 (S), R3.2, R7.2, R11.2, R14.2, TP4.1, TP5.1, TP6.1, U1.8 (GND), U1.18 (GND), U1.30 (GND), U1.38 (GND), U2.7 (GND), U2.18 (GND@1), U2.21 (GND@2), U2.25 (GND@A), U2.26 (TEST), U3.2 (GND), U4.2 (GND), U5.3 (GND), U6.1 (GND), U7.3 (GND), U8.3 (GND), U9.3 (GND)
unnamed: C4.1, U2.17 (3V3OUT)
unnamed: C6.1, J10.6
unnamed: C7.1, C8.1, D1.1 (K), R4.1, U4.5 (V_in)
unnamed: C9.1, D4.1 (K), L1.1, U4.6 (SW)
unnamed: C9.2, R5.2
unnamed: D3.1 (K), R5.1, U4.1 (Boost)
unnamed: D8.2 (A), R10.2
unnamed: Q1.1 (G), R8.1, R9.2
unnamed: Q2.3 (D), R8.2
unnamed: Q3.1 (G), R12.1, R13.2
unnamed: Q4.3 (D), R12.2
unnamed: R2.2, U2.19 (~RESET)
unnamed: R4.2, U4.4 (EN)
unnamed: R6.2, R7.1, U4.3 (V_FB)
VCC: R15.2, R16.2, R17.2, R18.2, U5.5 (VCC), U7.5 (VCC), U8.5 (VCC), U9.5 (VCC)

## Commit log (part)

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2023-08-31 Testing relative movement
2023-08-31 Testing speed parameter setting
2023-09-01 Updated to use upgraded NewScale interface
2023-09-05 Upgrade package and test new features
    linked speeds, flipped directions
2023-09-08 Upgraded NewScale package for requested visualizer features
    See issue #14 for requested changes
2023-09-12 Fixing shader workflow errors
2023-09-12 Probe visualizer prototype
2023-09-20 Update to latest ONIX package
    Built from source
2023-09-20 Proper closing of draw quad SelectMany
2023-09-20 Cleanup screen sync test
2023-09-21 Data collection for roundtrip
2023-10-13 Basic cubemap rendering
2023-10-17 Add proto tracking of current position and rotation
2023-10-17 Cleanup layout
2023-10-17 Working 3d translation, movement
2023-10-19 Correct sphere mapping prototype
2023-10-20 Config for python runtime testing
2023-10-24 Revert bonsai version for testing gratings
2023-10-25 Virtual grating movement in 1D
2023-10-26 Update parameters for 4-screen surround
2023-10-26 create insertion workflow, add neuropixels shader window visualizer
2023-10-26 Add stacked LFP and spike visualizers
2023-10-30 Completed logging workflow for insertion workflow
2023-10-31 Remove unnecessary planning files, streamline to Bonsai project
2023-10-31 Prototype schema implementation
2023-10-31 Implement prototype loading of session settings
2023-11-02 Prototype for trial sequence
2023-11-02 Example trial stimulus drawing
2023-11-02 Cleanup workflow
2023-11-02 Example gratings settings in schema
2023-11-02 Added dummy movement feedback
2023-11-02 Cleanup DoTrial logic
2023-11-03 Outline trial logic state machine
2023-11-03 Initial run threshold logic
2023-11-03 Rewrite initial trial logic
2023-11-06 Add halt running check
2023-11-06 Use trial halt probability for trial type randm choice
2023-11-06 Ignore jetbrains files
2023-11-22 Completed analysis scripts for video benchmarks
2023-11-30 Update benchmark workflows for Matrox only test
2023-11-30 Updated round trip analysis script for updated data
2023-11-30 Add data for 60hz
2023-11-30 Ignore idea files
2023-11-30 Added PMW3360 test workflow
2023-12-05 Removing obsolete FilterMessage
2023-12-05 Remove other obsolete FilterMessage
2023-12-05 Testing proportional control with PMW3360
2023-12-08 Template workflow for motion clouds
2023-12-08 Basic playback of motion clouds
2023-12-11 update gitignore to ignore image textures
2023-12-13 Update schema for block centric parameters
2023-12-13 Add workflow for testing template loading
2023-12-14 Example session template with new schema
2023-12-14 Add decay timestep as schema parameter
2023-12-14 Correct timer initialization from session settings
2024-01-05 Halt trial type decision state
2024-01-05 Use experiment events instead of DrawText calls
2024-01-10 Reset threshold distance calculation on each loop
2024-01-10 Block reset on timer expiration
2024-01-10 Add random halt delay
2024-01-10 Tidy up components in group workflows
2024-01-10 Remove obsolete trial logic code
2024-01-10 Initial logic for block visual stimulus selection
2024-01-10 Testing visual stimulus switch
2024-02-06 Minimal debug and basic analysis script
2024-02-08 Initial workflow and layout for debugging analog IO
2024-02-08 Completed analog IO debug workflow
2024-02-08 Add delay subscription test to debug analog IO bug
2024-02-08 Decouple IO initialisation from data streaming
2024-02-14 Externalise session settings to be editable in main workflow
2024-02-14 Add flow sensor input as movement delta source
2024-02-14 Added prototype motion cloud block to trial logic
2024-02-15 Add vestibularH1 interface package
2024-02-15 Add camera control logic
2024-02-15 Add motion cloud 'corridor' to visual env
2024-02-15 Modify schema to allow for block specific gain
2024-02-15 Restore fullscreen settings for demo
    Also added simple visualizer for experiment events
2024-02-27 Retesting propotional control workflow with PMW3360
2024-02-27 Add nuget version of aeon package
2024-02-27 Fix configure bug in local Aeon SpinnakerCapture
2024-02-27 Add Aeon style SpinnakerCapture
2024-02-27 Restore trial logic
2024-02-27 Add H2 interface as local package
2024-02-27 Replace dynamic HARP operators for H2 hardware
2024-02-27 Replace initialisation HARP operators for H2 hardware
2024-02-27 Test workflow with new operators
2024-04-03 Add a start logging key option
2024-04-03 Add experiment event for start logging
2024-04-04 Update schema to include further gain settings
2024-04-04 Add basic H2 device logic
2024-04-04 Add initial H2 reset
2024-04-04 Initial block type example with inheritance
2024-04-04 Testing instantiation of block types
2024-04-04 Update schema to provide vis stim extents as well as offsets
2024-04-04 Update stimulus fields with schema parameters
2024-04-09 Add mouse wheel input for debug
2024-04-09 Add alias property to schema
2024-04-09 Generate interface for new schema
2024-04-09 Create variable source for block gain
2024-04-09 Modifiable visual flow sources
    FlowX, FlowY, rotarty motion and playback source all contribute to phase procession, according to gain set in schema.
2024-04-09 Initial motor procession calculation
2024-04-09 Creation of motor pulse command
2024-04-10 Testing motor control with new schema parameters
2024-04-10 Use CombineLatest for motor procession calculation
2024-04-10 Remove mouse wheel debug
    Dangerous while motor is turned on!
2024-04-10 Add homing functionality
    Added homing command, CW and CCW step commands. Home platform on each block.
2024-04-10 Testing new block logic
2024-04-30 visual stimuli workflows
2024-05-03 npx new workflows and bonsai config
2024-05-03 npx new workflows
2024-05-03 test fokder
2024-05-03 syncronize
2024-05-04 added matrix writer nodes and headstage port control
2024-05-04 np1.0 headstage workflow for streaming and saving
2024-05-04 file organisation
2024-05-06 correct Sync workflow
2024-05-07 Sync workflow for test
2024-05-10 wallpaper
2024-05-10 corridor_FOE
2024-05-10 cam trigger 30 hz
2024-05-10 spatial freq
2024-05-16 INFINITE CORRIDOR_FOE
2024-05-17 H1 com switch
2024-05-17 change fs and triggwidth
2024-06-04 switched COMs in Main
2024-06-05 schema updated
2024-06-05 disabled ttl
2024-06-05 corridor stimulus initial commit
2024-06-07 orthopgraphic view
    Set spatial frequency as total number of cycles per 360 degrees
2024-06-12 new insertion workflow
2024-06-13 changes in insertion workflow
2024-06-19 hilde sync test_ removed start key press
2024-06-19 openephys socket test
2024-06-26 motor_gain_test_yml_files
2024-06-27 Update local schema for named array payload
2024-07-02 Add prototype test workflow for screen sync quad logic
2024-07-03 motor test gain yml with ede
2024-07-09 yml file org
2024-07-09 Initial sampling test
2024-07-09 Prototype logic for photometry sync
2024-07-09 Add logging for ONIX streams
2024-07-11 Fix halt event placement
2024-07-11 Revert back from mouse wheel debug
2024-07-18 Alternate motor signal sampling approach
2024-07-18 Blocks return a value only when complete
2024-07-19 Longer initial runtime for testing
2024-07-19 Testing sync quad in main workflow
2024-07-19 Basic playback file conversion script
2024-07-19 Proto cleanup
2024-07-19 Update schema with playback file
2024-07-19 Reimplement playback source
2024-07-19 Testing playback source
2024-07-19 Update data schema extension
2024-07-19 Add run gains to main workflow
2024-07-23 Add experiment event logging
2024-07-26 changed quad position
2024-07-26 updated training session yml
2024-08-12 Initial documentation
2024-08-12 Environment documentation
2024-08-12 Schema specifics documentation
2024-08-12 Complete basic setup documentation
2024-09-13 main_workflow_screensyncquad
2024-09-16 Initialise motor playback with 0
2024-09-16 Add temp data paths
2024-09-16 Add a notebook for photometry sync examples
2024-09-17 Use aeon api for device loading
2024-09-19 Onix timestamp mapping
2024-09-19 Photometry stream reader
2024-09-19 Notes for next steps
2024-09-20 Add aligned photometry to figure
2024-09-20 Add new ONIX packages
2024-09-20 Update layout for main visualizer
2024-09-24 Remove defunct local packages
2024-09-24 Add a better harp sync monitor
2024-09-24 Update motion cloud test with named texture
2024-09-24 Add texture folder extension to main workflow
2024-09-24 Update schema for named texture rather than path
2024-09-24 Example texture file loading
2024-09-25 Modify regression for onix synchronisation
2024-09-26 Simple notebook for encoder vs. flow sanity check
2024-09-26 Subscribe to raw and buffer analog streams simultaneously
2024-09-27 Example access of texture sequence data
2024-09-27 Add extra example texture to TextureResources
2024-09-27 Add test schema for switching motion clouds
2024-09-27 Divide by zero checking
2024-10-03 Fix initial texture data loading bug
2024-10-03 Add smoother movement delta to main workflow
2024-10-16 Fix texture frame initialisation bug
    If a longer texture is initially loaded, followed by a shorter one, BindTexture will initially try and load the last indexed frame which may be out of bounds of the longer texture length. Fix by alwa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
2024-10-16 Testing playback with motion clouds
2024-10-16 Example generating a valid sin wave playback file
2024-10-16 Update prepare-playback_file and test
2024-10-16 Revert back from debug movement delta
2024-10-19 linear_drift_playback
2024-10-19 new yml for rotation
2024-10-19 int16 conversion
2024-10-19 update smooth int16 drift
2024-10-19 drift
2024-10-19 10000
2024-10-22 new playback
2024-10-22 yml files
2024-10-31 Added some example schemas for different playback blockls
2024-10-31 Update schema to allow for more control over delta switches
2024-10-31 Implement reverse halt attempt
2024-10-31 Implement reverse halt and fix delta setting in ApplyHalth
2024-10-31 Revert from debug motion mode
2024-10-31 Add motion smoothing parameter to schema
2024-10-31 Implement flow smoothing in main workflow
2024-10-31 Add schema parameters for cameras to main workflow
2024-10-31 Update aeon package and add gain parameters to cameras
2024-11-14 Interval latency test
2024-11-15 Add initial analysis script
2024-11-15 Mean and std analysis for pulse to encoder time
2024-11-15 Full latency analysis
2024-12-18 Remove comma in experiment event
2025-01-09 Log digital input state as integer rather than enum
2025-01-13 yml_workflow_changes
2025-01-15 Update postprocessing script for new digital input bitmask logging
2025-01-15 Revert Aeon package and remove gain parameters
2025-01-15 Minimal notebook to try and reproduce bug
2025-01-16 Add python environment instructions to readme
2025-01-16 Fix readme typo
2025-01-23 Fix pulses initiation issue
2025-02-05 added .DS_Store to gitignore
2025-02-06 workflow and drivers
2025-02-07 wf changes
2025-02-12 Enable heartbeats in Harp devices
2025-02-13 new yml files and change in screen res on main wf
2025-02-17 added cloud to textures, removed old one.
2025-02-24 Ignore sleap files
2025-02-24 Remove hubclock logging from main workflow
2025-02-26 Revert "added heartbeat to H1 and H2 .yml files"
2025-02-27 Add initial workflow for arena
2025-02-27 Add basic screen mapping
2025-03-06 Rotation calculations
2025-03-06 Translation calculations
2025-03-06 Only need to do forward vector calculation
2025-03-06 Add views for all 4 screens
2025-03-06 Add some models and placements
2025-03-06 Prototype arena
2025-03-10 use encoder reading to affect forward vector
2025-03-11 Add position limits for arena
2025-03-11 Testing model drawing in arena
2025-03-11 Add screen sync quad
2025-03-11 Testing screen sync quad
2025-03-11 Logging of current relevant data streams
2025-03-12 Fix S16 overflow in encoder diff values
2025-03-12 Overflow difference operator
2025-03-12 Add environment objects
2025-03-17 Add logging for position and forward vector
2025-04-18 Notes on data acquisition
2025-04-18 Notes on gain settings
2025-04-18 Flow sensor smoothing notes
2025-04-18 Homing speed settable as part of schema
2025-04-21 Sleap training steps
2025-04-21 Sleap example
2025-04-23 Fix key down subscription for trial logic
2025-04-23 yml change
2025-04-29 new ymll file
2025-04-30 new yml
2025-10-01 new yml
    added yml file to src to be used in next experiments
2025-11-29 Update README.md
    with current Spinnaker download path
2025-12-02 added timestamp diff visualisers for cameras
2025-12-02 added brightness histogram for flow sensor
